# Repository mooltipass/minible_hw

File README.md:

# minible_hw
Repository for the Mini BLE Hardware

## Licenses

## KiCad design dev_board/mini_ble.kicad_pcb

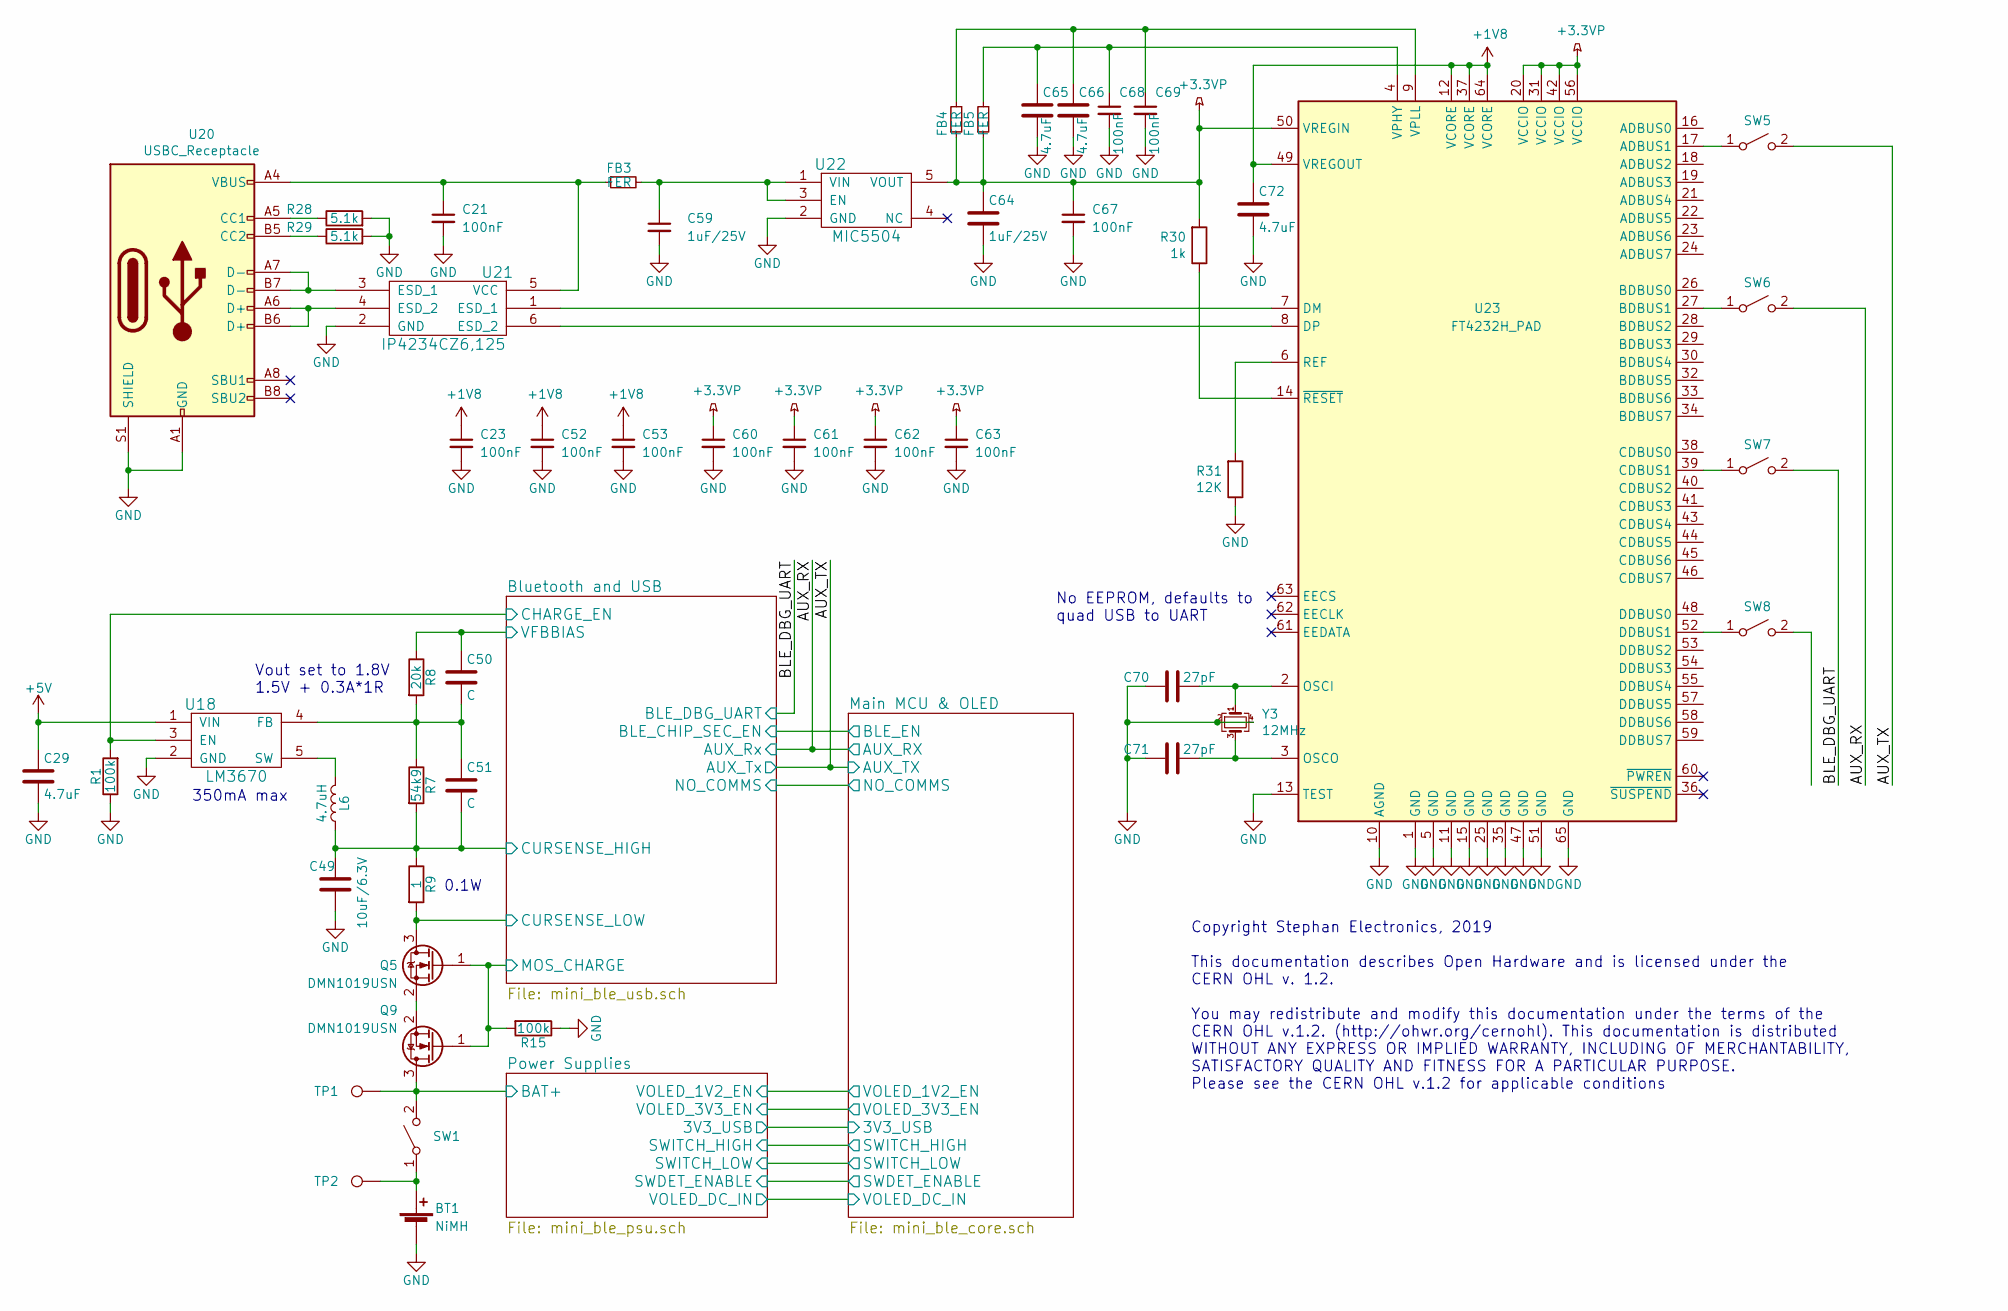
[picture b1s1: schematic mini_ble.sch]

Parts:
BT1: NiMH; BAT_TWOTHIRD_AAA
C21, C23, C52, C53, C60, C61, C62, C63, C67, C68, C69: 100nF; C_0603_1608Metric
C29, C65, C66, C72: 4.7uF; C_0603_1608Metric
C49: 10uF/6.3V; C_0603_1608Metric
C50, C51: C; C_0402_1005Metric
C59, C64: 1uF/25V; C_0603_1608Metric
C70, C71: 27pF; C_0402_1005Metric
FB3, FB4, FB5: FER; R_0603_1608Metric
L6: 4.7uH; L_0805_2012Metric
Q5, Q9: DMN1019USN; SC-59
R1, R15: 100k; R_0402_1005Metric
R7: 54k9; R_0402_1005Metric
R8: 20k; R_0402_1005Metric
R9: 1; R_0603_1608Metric
R28, R29: 5.1k; R_0402_1005Metric
R30: 1k; R_0402_1005Metric
R31: 12K; R_0402_1005Metric
SW1, SW5, SW6, SW7, SW8: SW_SPST; DIP_1POS_KAE01LAGT
TP1, TP2: TestPoint; TP_KEYSTONE_500X
U18: LM3670; SOT-23-5
U20: USBC_Receptacle; USB_C_Receptacle_GT-USB-7010
U21: IP4234CZ6,125; TSOP-6_1.65x3.05mm_P0.95mm
U22: MIC5504; SOT-23-5
U23: FT4232H_PAD; QFN-64-1EP_9x9mm_P0.5mm_EP4.35x4.35mm
Y3: 12MHz; Crystal_SMD_2520-4Pin_2.5x2.0mm

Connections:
+1V5: Q9.3 (D), SW1.2 (B), TP1.1; also elsewhere on the board
+1V8: C23.1, C52.1, C53.1, C72.1, U23.12 (VCORE), U23.37 (VCORE), U23.49 (VREGOUT), U23.64 (VCORE)
+3.3VP: C60.1, C61.1, C62.1, C63.1, C64.1, C67.1, FB4.1, FB5.1, R30.2, U22.5 (VOUT), U23.20 (VCCIO), U23.31 (VCCIO), U23.42 (VCCIO), U23.50 (VREGIN), U23.56 (VCCIO)
+5V: C29.1, U18.1 (VIN); also elsewhere on the board
/AUX_RX: SW6.2 (B); also elsewhere on the board
/AUX_TX: SW5.2 (B); also elsewhere on the board
/BLE_DBG_UART: SW7.2 (B); also elsewhere on the board
/Bluetooth and USB/CHARGE_EN: R1.2, U18.3 (EN); also elsewhere on the board
/Bluetooth and USB/CURSENSE_HIGH: C49.1, C51.2, L6.1, R7.2, R9.1; also elsewhere on the board
/Bluetooth and USB/CURSENSE_LOW: Q5.3 (D), R9.2; also elsewhere on the board
/Bluetooth and USB/MOS_CHARGE: Q5.1 (G), Q9.1 (G), R15.2; also elsewhere on the board
/Bluetooth and USB/VFBBIAS: C50.1, R8.1; also elsewhere on the board
GND: BT1.2 (-), C21.2, C23.2, C29.2, C49.2, C52.2, C53.2, C59.2, C60.2, C61.2, C62.2, C63.2, C64.2, C65.2, C66.2, C67.2, C68.2, C69.2, C70.1, C71.1, C72.2, R1.1, R15.1, R28.2, R29.2, R31.1, U18.2 (GND), U20.A1 (GND), U20.A12 (GND), U20.B1 (GND), U20.B12 (GND), U20.S1 (SHIELD), U21.2 (GND), U22.2 (GND), U23.1 (GND), U23.5 (GND), U23.10 (AGND), U23.11 (GND), U23.13 (TEST), U23.15 (GND), U23.25 (GND), U23.35 (GND), U23.47 (GND), U23.51 (GND), U23.65 (GND), Y3.2, Y3.4; also elsewhere on the board
unnamed: BT1.1 (+), SW1.1 (A), TP2.1
unnamed: C21.1, FB3.1, U20.A4 (VBUS), U20.A9 (VBUS), U20.B4 (VBUS), U20.B9 (VBUS), U21.5 (VCC)
unnamed: C50.2, C51.1, R7.1, R8.2, U18.4 (FB)
unnamed: C59.1, FB3.2, U22.1 (VIN), U22.3 (EN)
unnamed: C65.1, C68.1, FB5.2, U23.4 (VPHY)
unnamed: C66.1, C69.1, FB4.2, U23.9 (VPLL)
unnamed: C70.2, U23.2 (OSCI), Y3.1
unnamed: C71.2, U23.3 (OSCO), Y3.3
unnamed: L6.2, U18.5 (SW)
unnamed: Q5.2 (S), Q9.2 (S)
unnamed: R28.1, U20.A5 (CC1)
unnamed: R29.1, U20.B5 (CC2)
unnamed: R30.1, U23.14 (~RESET)
unnamed: R31.2, U23.6 (REF)
unnamed: SW5.1 (A), U23.17 (ADBUS1)
unnamed: SW6.1 (A), U23.27 (BDBUS1)
unnamed: SW7.1 (A), U23.39 (CDBUS1)
unnamed: SW8.1 (A), U23.52 (DDBUS1)
unnamed: U20.A6 (D+), U20.B6 (D+), U21.4 (ESD_2)
unnamed: U20.A7 (D-), U20.B7 (D-), U21.3 (ESD_1)
unnamed: U21.1 (ESD_1), U23.7 (DM)
unnamed: U21.6 (ESD_2), U23.8 (DP)

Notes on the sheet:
Copyright Stephan Electronics, 2019 This documentation describes Open Hardware and is licensed under the CERN OHL v. 1.2. You may redistribute and modify this documentation under the terms of the CERN OHL v.1.2. (http://ohwr.org/cernohl). This documentation is distributed WITHOUT ANY EXPRESS OR IMP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
350mA max
Vout set to 1.8V 1.5V + 0.3A*1R
0.1W
No EEPROM, defaults to quad USB to UART

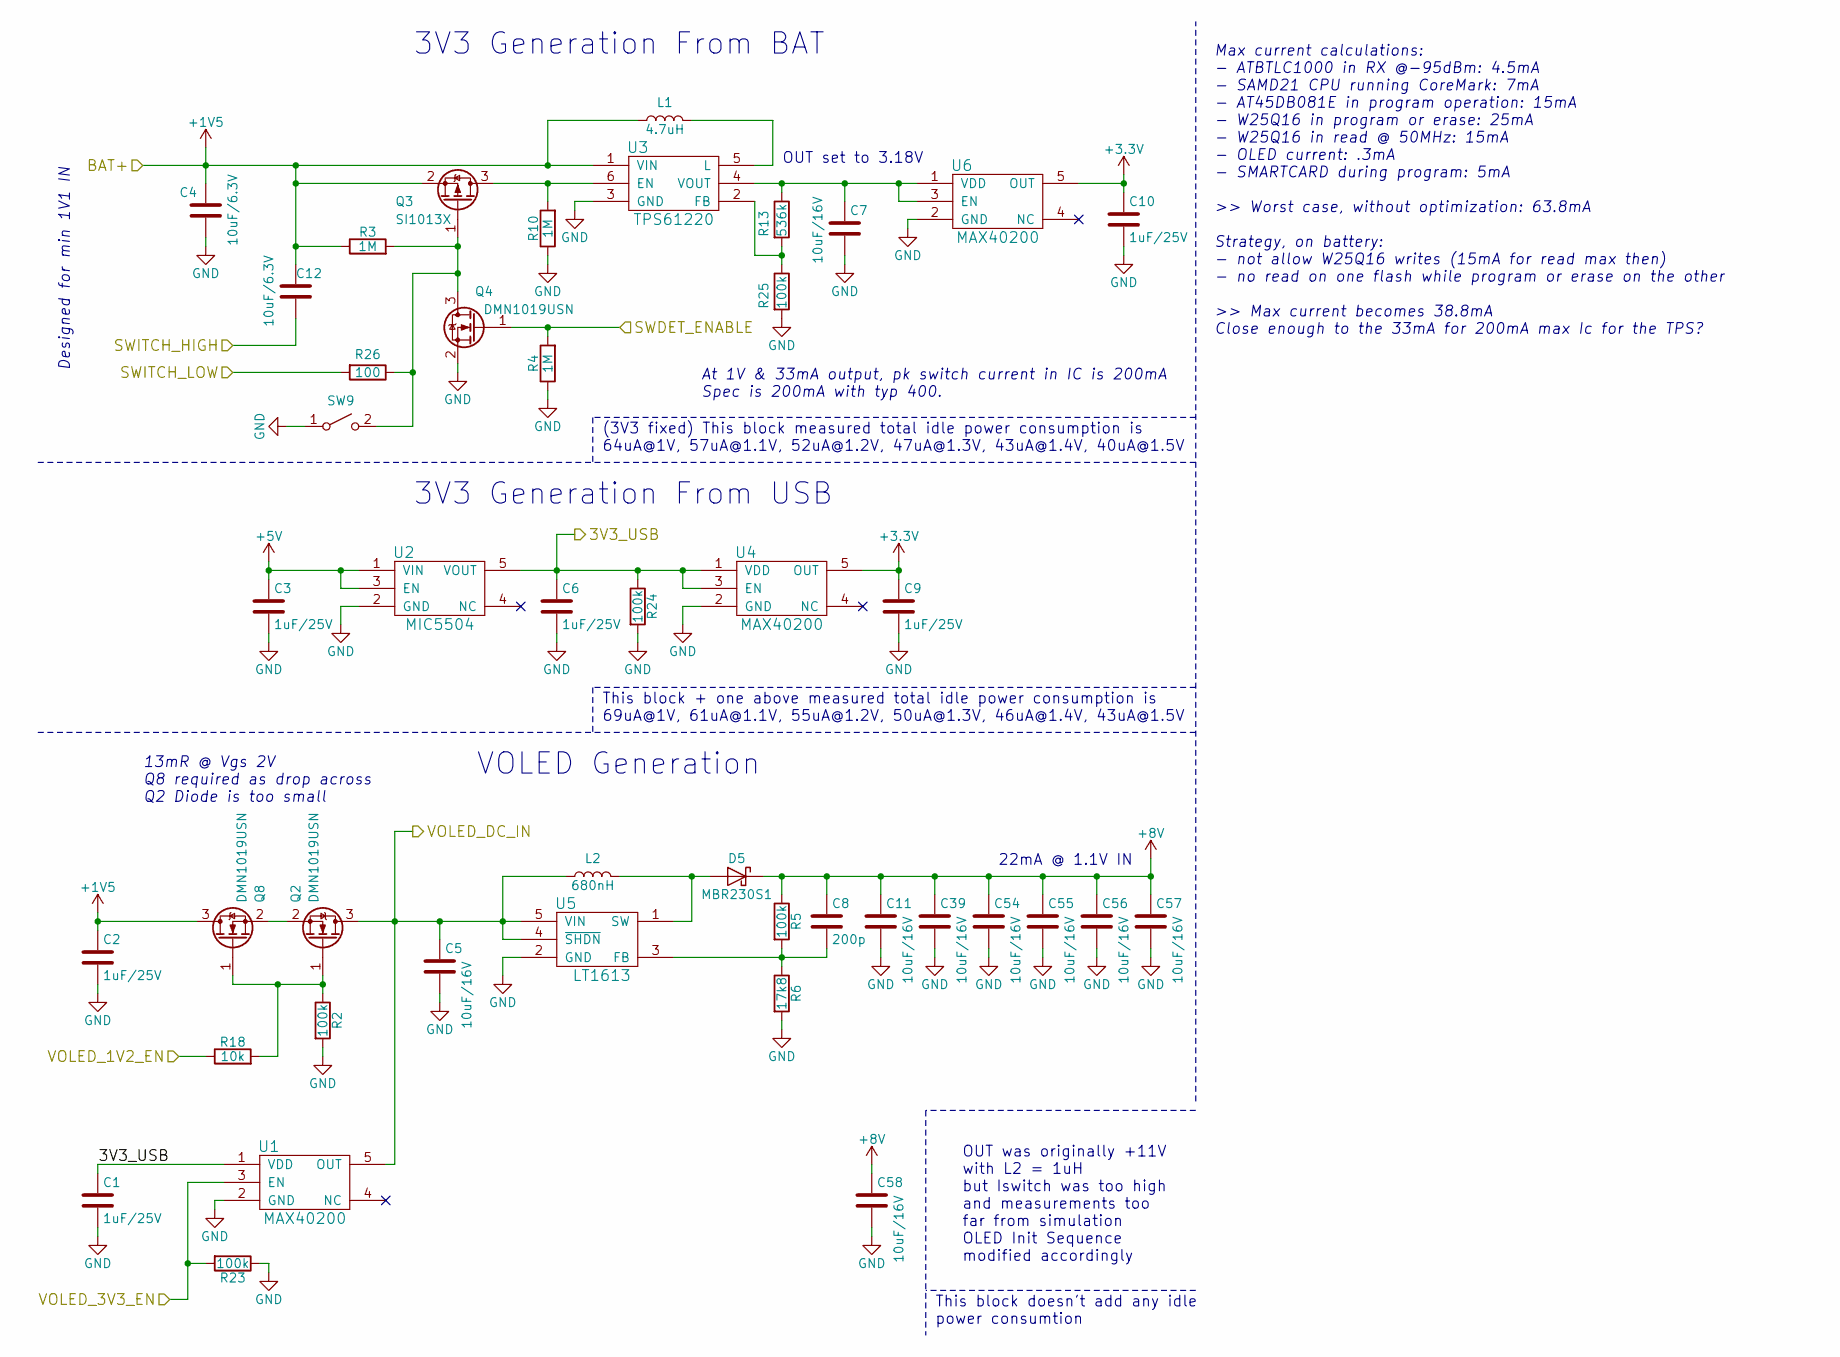
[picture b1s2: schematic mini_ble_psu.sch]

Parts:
C1, C2, C3, C6, C9, C10: 1uF/25V; C_0603_1608Metric
C4, C12: 10uF/6.3V; C_0603_1608Metric
C5, C7, C11, C39, C54, C55, C56, C57, C58: 10uF/16V; C_0805_2012Metric
C8: 200p; C_0402_1005Metric
D5: MBR230S1; D_SOD-123F
L1: 4.7uH; L_0805_2012Metric
L2: 680nH; L_0806
Q2, Q4, Q8: DMN1019USN; SC-59
Q3: SI1013X; SC89
R2, R5, R23, R24, R25: 100k; R_0402_1005Metric
R3, R4, R10: 1M; R_0402_1005Metric
R6: 17k8; R_0402_1005Metric
R13: 536k; R_0402_1005Metric
R18: 10k; R_0402_1005Metric
R26: 100; R_0402_1005Metric
SW9: SW_SPST; SWITCH_PUSH_6X3.5mm
U1, U4, U6: MAX40200; SOT-23-5
U2: MIC5504; SOT-23-5
U3: TPS61220; SOT-363_SC-70-6
U5: LT1613; TSOT-23-5

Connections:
+1V5: C2.1, C4.1, C12.1, L1.1, Q3.2 (S), Q8.3 (D), R3.1, U3.1 (VIN); also elsewhere on the board
+5V: C3.1, U2.1 (VIN), U2.3 (EN); also elsewhere on the board
+8V: C8.1, C11.1, C39.1, C54.1, C55.1, C56.1, C57.1, C58.1, D5.1 (K), R5.1; also elsewhere on the board
/Main MCU & OLED/3V3_USB: C1.1, C6.1, R24.1, U1.1 (VDD), U2.5 (VOUT), U4.1 (VDD), U4.3 (EN); also elsewhere on the board
/Main MCU & OLED/SWDET_ENABLE: Q4.1 (G), R4.2; also elsewhere on the board
/Main MCU & OLED/SWITCH_HIGH: C12.2; also elsewhere on the board
/Main MCU & OLED/SWITCH_LOW: R26.2; also elsewhere on the board
/Main MCU & OLED/VOLED_1V2_EN: R18.1; also elsewhere on the board
/Main MCU & OLED/VOLED_3V3_EN: R23.2, U1.3 (EN); also elsewhere on the board
/Main MCU & OLED/VOLED_DC_IN: C5.1, L2.1, Q2.3 (D), U1.5 (OUT), U5.4 (~SHDN), U5.5 (VIN); also elsewhere on the board
GND: C1.2, C2.2, C3.2, C4.2, C5.2, C6.2, C7.2, C9.2, C10.2, C11.2, C39.2, C54.2, C55.2, C56.2, C57.2, C58.2, Q4.2 (S), R2.2, R4.1, R6.2, R10.1, R23.1, R24.2, R25.2, SW9.1 (A), U1.2 (GND), U2.2 (GND), U3.3 (GND), U4.2 (GND), U5.2 (GND), U6.2 (GND); also elsewhere on the board
unnamed: C7.1, R13.1, U3.4 (VOUT), U6.1 (VDD), U6.3 (EN)
unnamed: C8.2, R5.2, R6.1, U5.3 (FB)
unnamed: D5.2 (A), L2.2, U5.1 (SW)
unnamed: L1.2, U3.5 (L)
unnamed: Q2.1 (G), Q8.1 (G), R2.1, R18.2
unnamed: Q2.2 (S), Q8.2 (S)
unnamed: Q3.1 (G), Q4.3 (D), R3.2, R26.1, SW9.2 (B)
unnamed: Q3.3 (D), R10.2, U3.6 (EN)
unnamed: R13.2, R25.1, U3.2 (FB)

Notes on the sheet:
3V3 Generation From USB
3V3 Generation From BAT
VOLED Generation
At 1V & 33mA output, pk switch current in IC is 200mA Spec is 200mA with typ 400.
Max current calculations: - ATBTLC1000 in RX @-95dBm: 4.5mA - SAMD21 CPU running CoreMark: 7mA - AT45DB081E in program operation: 15mA - W25Q16 in program or erase: 25mA - W25Q16 in read @ 50MHz: 15mA - OLED current: .3mA - SMARTCARD during program: 5mA >> Worst case, without optimization: 63.8mA S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
Designed for min 1V1 IN
13mR @ Vgs 2V Q8 required as drop across Q2 Diode is too small
(3V3 fixed) This block measured total idle power consumption is 64uA@1V, 57uA@1.1V, 52uA@1.2V, 47uA@1.3V, 43uA@1.4V, 40uA@1.5V
This block + one above measured total idle power consumption is 69uA@1V, 61uA@1.1V, 55uA@1.2V, 50uA@1.3V, 46uA@1.4V, 43uA@1.5V
This block doesn't add any idle power consumtion
22mA @ 1.1V IN
OUT was originally +11V with L2 = 1uH but Iswitch was too high and measurements too far from simulation OLED Init Sequence modified accordingly
OUT set to 3.18V

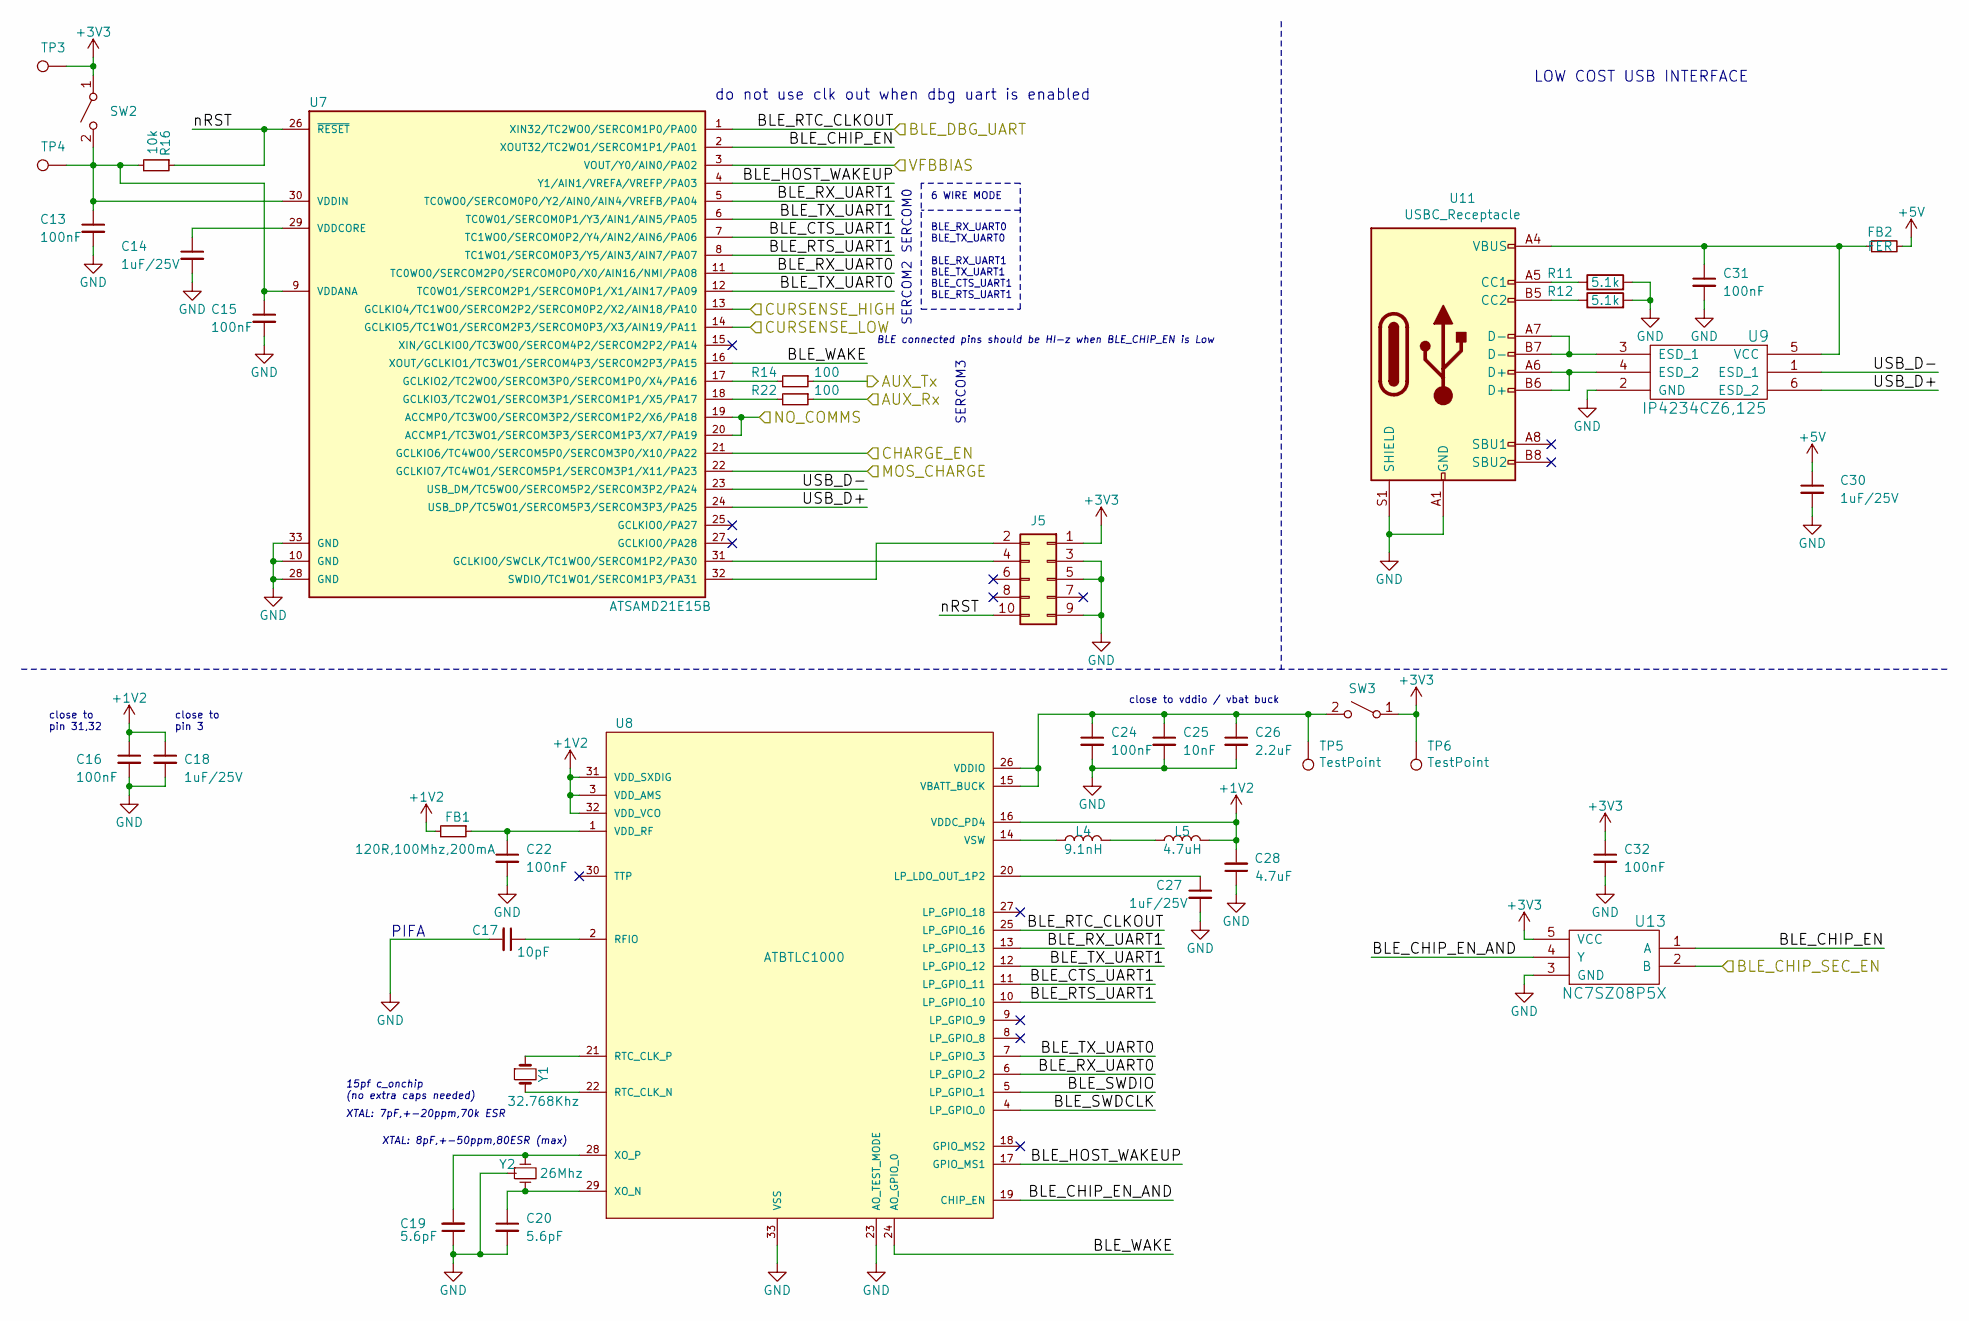
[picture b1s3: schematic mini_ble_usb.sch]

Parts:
C13, C15, C16, C22, C24, C31, C32: 100nF; C_0603_1608Metric
C14, C18, C27, C30: 1uF/25V; C_0603_1608Metric
C17: 10pF; C_0402_1005Metric
C19, C20: 5.6pF; C_0402_1005Metric
C25: 10nF; C_0603_1608Metric
C26: 2.2uF; C_0603_1608Metric
C28: 4.7uF; C_0603_1608Metric
FB1: 120R,100Mhz,200mA; R_0603_1608Metric
FB2: FER; R_0603_1608Metric
J5: Conn_02x05_Odd_Even; SHF-105-01-X-D-TH
L4: 9.1nH; L_0603_1608Metric
L5: 4.7uH; L_0805_2012Metric
R11, R12: 5.1k; R_0402_1005Metric
R14, R22: 100; R_0402_1005Metric
R16: 10k; R_0402_1005Metric
SW2, SW3: SW_SPST; DIP_1POS_KAE01LAGT
TP3, TP4, TP5, TP6: TestPoint; TP_KEYSTONE_500X
U7: ATSAMD21E15B; QFN-32-1EP_5x5mm_P0.5mm_EP3.7x3.7mm
U8: ATBTLC1000; QFN-32-1EP_4x4mm_Pitch0.4mm
U9: IP4234CZ6,125; TSOP-6_1.65x3.05mm_P0.95mm
U11: USBC_Receptacle; USB_C_Receptacle_GT-USB-7010
U13: NC7SZ08P5X; SOT-353_SC-70-5
Y1: 32.768Khz; Crystal_SMD_3215-2Pin_3.2x1.5mm
Y2: 26Mhz; Crystal_SMD_2016-4Pin_2.0x1.6mm

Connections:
+1V2: C16.1, C18.1, C28.2, FB1.2, L5.2, U8.3 (VDD_AMS), U8.16 (VDDC_PD4), U8.31 (VDD_SXDIG), U8.32 (VDD_VCO)
+5V: C30.1, FB2.2; also elsewhere on the board
/AUX_RX: R22.1; also elsewhere on the board
/AUX_TX: R14.1; also elsewhere on the board
/BLE_DBG_UART: U7.1 (XIN32/TC2WO0/SERCOM1P0/PA00), U8.25 (LP_GPIO_16); also elsewhere on the board
/Bluetooth and USB/BLE_CHIP_EN: U7.2 (XOUT32/TC2WO1/SERCOM1P1/PA01), U13.1 (A)
/Bluetooth and USB/BLE_CHIP_EN_AND: U8.19 (CHIP_EN), U13.4 (Y)
/Bluetooth and USB/BLE_CHIP_SEC_EN: U13.2 (B); also elsewhere on the board
/Bluetooth and USB/BLE_CTS_UART1: U7.7 (TC1WO0/SERCOM0P2/Y4/AIN2/AIN6/PA06), U8.11 (LP_GPIO_11)
/Bluetooth and USB/BLE_HOST_WAKEUP: U7.4 (Y1/AIN1/VREFA/VREFP/PA03), U8.17 (GPIO_MS1)
/Bluetooth and USB/BLE_RTS_UART1: U7.8 (TC1WO1/SERCOM0P3/Y5/AIN3/AIN7/PA07), U8.10 (LP_GPIO_10)
/Bluetooth and USB/BLE_RX_UART0: U7.11 (TC0WO0/SERCOM2P0/SERCOM0P0/X0/AIN16/NMI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), U8.6 (LP_GPIO_2)
/Bluetooth and USB/BLE_RX_UART1: U7.5 (TC0WO0/SERCOM0P0/Y2/AIN0/AIN4/VREFB/PA04), U8.13 (LP_GPIO_13)
/Bluetooth and USB/BLE_SWDCLK: U8.4 (LP_GPIO_0)
/Bluetooth and USB/BLE_SWDIO: U8.5 (LP_GPIO_1)
/Bluetooth and USB/BLE_TX_UART0: U7.12 (TC0WO1/SERCOM2P1/SERCOM0P1/X1/AIN17/PA09), U8.7 (LP_GPIO_3)
/Bluetooth and USB/BLE_TX_UART1: U7.6 (TC0W01/SERCOM0P1/Y3/AIN1/AIN5/PA05), U8.12 (LP_GPIO_12)
/Bluetooth and USB/BLE_WAKE: U7.16 (XOUT/GCLKIO1/TC3WO1/SERCOM4P3/SERCOM2P3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), U8.24 (AO_GPIO_0)
/Bluetooth and USB/CHARGE_EN: U7.21 (GCLKIO6/TC4WO0/SERCOM5P0/SERCOM3P0/X10/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); also elsewhere on the board
/Bluetooth and USB/CURSENSE_HIGH: U7.13 (GCLKIO4/TC1WO0/SERCOM2P2/SERCOM0P2/X2/A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); also elsewhere on the board
/Bluetooth and USB/CURSENSE_LOW: U7.14 (GCLKIO5/TC1WO1/SERCOM2P3/SERCOM0P3/X3/A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); also elsewhere on the board
/Bluetooth and USB/MOS_CHARGE: U7.22 (GCLKIO7/TC4WO1/SERCOM5P1/SERCOM3P1/X11/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); also elsewhere on the board
/Bluetooth and USB/NO_COMMS: U7.19 (ACCMP0/TC3WO0/SERCOM3P2/SERCOM1P2/X6/PA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), U7.20 (ACCMP1/TC3WO1/SERCOM3P3/SERCOM1P3/X7/PA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); also elsewhere on the board
/Bluetooth and USB/USB_D+: U7.24 (USB_DP/TC5WO1/SERCOM5P3/SERCOM3P3/PA25), U9.6 (ESD_2)
/Bluetooth and USB/USB_D-: U7.23 (USB_DM/TC5WO0/SERCOM5P2/SERCOM3P2/PA24), U9.1 (ESD_1)
/Bluetooth and USB/VFBBIAS: U7.3 (VOUT/Y0/AIN0/PA02); also elsewhere on the board
/Bluetooth and USB/nRST: J5.10, R16.1, U7.26 (~RESET~)
GND: C13.2, C14.2, C15.2, C16.2, C17.2, C18.2, C19.1, C20.2, C22.2, C24.2, C25.2, C26.2, C27.2, C28.1, C30.2, C31.2, C32.2, J5.3, J5.5, J5.9, R11.2, R12.2, U7.10 (GND), U7.28 (GND), U7.33 (GND), U8.23 (AO_TEST_MODE), U8.33 (VSS), U9.2 (GND), U11.A1 (GND), U11.A12 (GND), U11.B1 (GND), U11.B12 (GND), U11.S1 (SHIELD), U13.3 (GND), Y2.2, Y2.4; also elsewhere on the board
unnamed: C13.1, C15.1, R16.2, SW2.2 (B), TP4.1, U7.9 (VDDANA), U7.30 (VDDIN)
unnamed: C14.1, U7.29 (VDDCORE)
unnamed: C17.1, U8.2 (RFIO)
unnamed: C19.2, U8.28 (XO_P), Y2.1
unnamed: C20.1, U8.29 (XO_N), Y2.3
unnamed: C22.1, FB1.1, U8.1 (VDD_RF)
unnamed: C24.1, C25.1, C26.1, SW3.2 (B), TP5.1, U8.15 (VBATT_BUCK), U8.26 (VDDIO)
unnamed: C27.1, U8.20 (LP_LDO_OUT_1P2)
unnamed: C31.1, FB2.1, U9.5 (VCC), U11.A4 (VBUS), U11.A9 (VBUS), U11.B4 (VBUS), U11.B9 (VBUS)
unnamed: J5.2, U7.32 (SWDIO/TC1WO1/SERCOM1P3/PA31)
unnamed: J5.4, U7.31 (GCLKIO0/SWCLK/TC1WO0/SERCOM1P2/PA30)
unnamed: L4.1, U8.14 (VSW)
unnamed: L4.2, L5.1
unnamed: R11.1, U11.A5 (CC1)
unnamed: R12.1, U11.B5 (CC2)
unnamed: R14.2, U7.17 (GCLKIO2/TC2WO0/SERCOM3P0/SERCOM1P0/X4/P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)
unnamed: R22.2, U7.18 (GCLKIO3/TC2WO1/SERCOM3P1/SERCOM1P1/X5/P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)
unnamed: U8.21 (RTC_CLK_P), Y1.1
unnamed: U8.22 (RTC_CLK_N), Y1.2
unnamed: U9.4 (ESD_2), U11.A6 (D+), U11.B6 (D+)
unnamed: U9.3 (ESD_1), U11.A7 (D-), U11.B7 (D-)

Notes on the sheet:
XTAL: 8pF,+-50ppm,80ESR (max)
XTAL: 7pF,+-20ppm,70k ESR
15pf c_onchip (no extra caps needed)
BLE connected pins should be HI-z when BLE_CHIP_EN is Low
close to vddio / vbat buck
LOW COST USB INTERFACE
close to pin 3
close to pin 31,32
SERCOM3
SERCOM2
SERCOM0
6 WIRE MODE
BLE_RX_UART0 BLE_TX_UART0 BLE_RX_UART1 BLE_TX_UART1 BLE_CTS_UART1 BLE_RTS_UART1
PIFA
do not use clk out when dbg uart is enabled

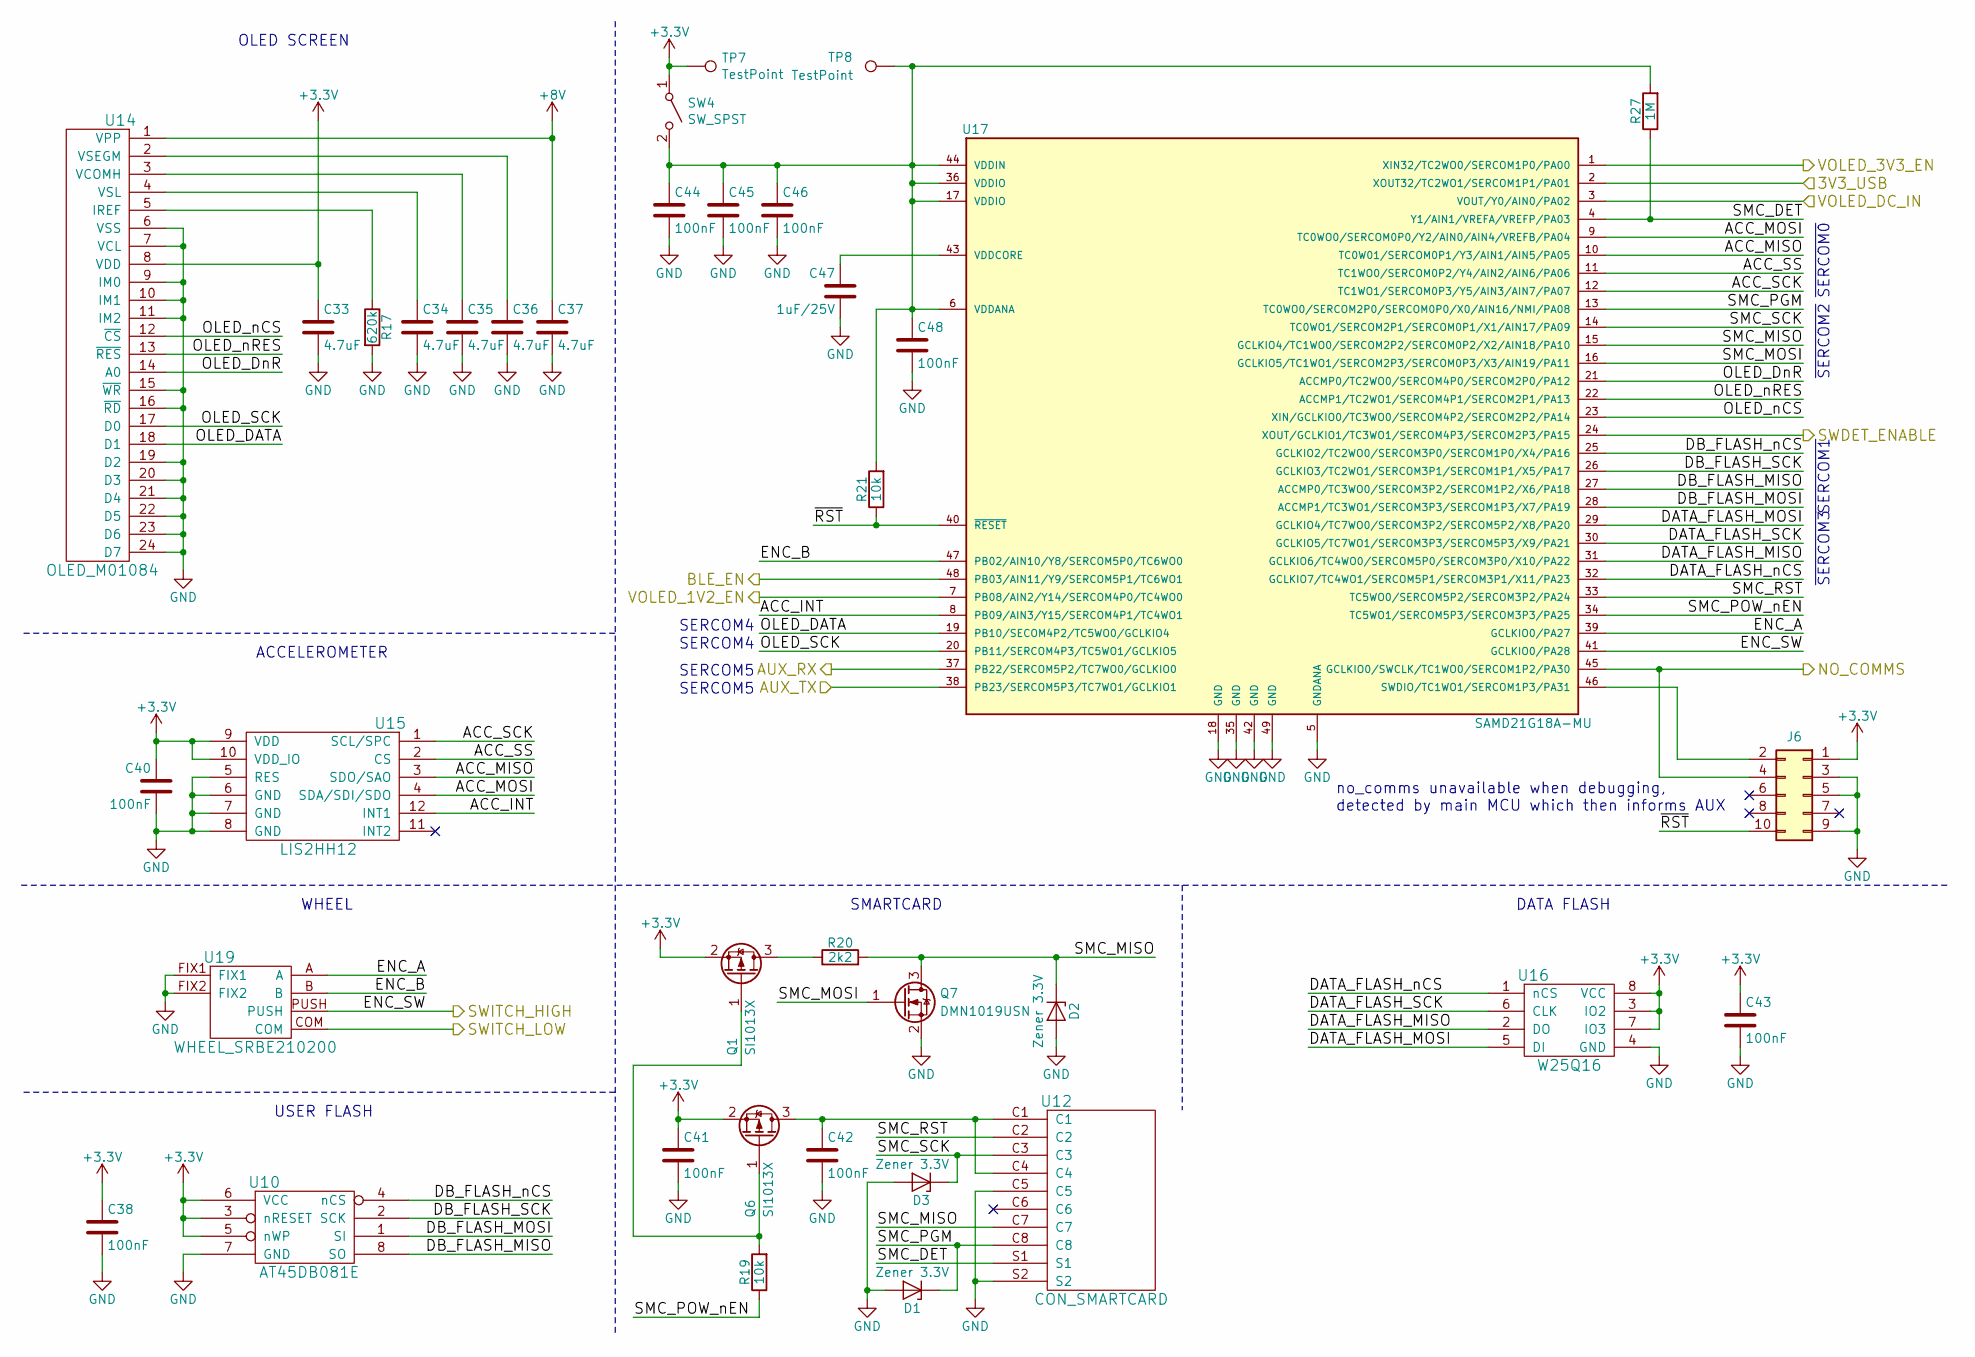
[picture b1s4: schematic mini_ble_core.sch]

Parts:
C33, C34, C35, C36, C37: 4.7uF; C_0603_1608Metric
C38, C40, C41, C42, C43, C44, C45, C46, C48: 100nF; C_0603_1608Metric
C47: 1uF/25V; C_0603_1608Metric
D1, D2, D3: Zener 3.3V; D_SOD-523
J6: Conn_02x05_Odd_Even; SHF-105-01-X-D-TH
Q1, Q6: SI1013X; SC89
Q7: DMN1019USN; SC-59
R17: 620k; R_0603_1608Metric
R19, R21: 10k; R_0402_1005Metric
R20: 2k2; R_0603_1608Metric
R27: 1M; R_0402_1005Metric
SW4: SW_SPST; DIP_1POS_KAE01LAGT
TP7, TP8: TestPoint; TP_KEYSTONE_500X
U10: AT45DB081E; SOIC-8_3.9x4.9mm_P1.27mm
U12: CON_SMARTCARD; CON_SMARTCARD_CLONE_91-90473-003A
U14: OLED_M01084; SCREEN_M01084
U15: LIS2HH12; LGA-12
U16: W25Q16; SOIC-8_3.9x4.9mm_P1.27mm
U17: SAMD21G18A-MU; QFN-48-1EP_7x7mm_P0.5mm_EP5.3x5.3mm
U19: WHEEL_SRBE210200; SRBE210200

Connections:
+8V: C37.1, U14.1 (VPP); also elsewhere on the board
/AUX_RX: U17.37 (PB22/SERCOM5P2/TC7WO0/GCLKIO0); also elsewhere on the board
/AUX_TX: U17.38 (PB23/SERCOM5P3/TC7WO1/GCLKIO1); also elsewhere on the board
/Bluetooth and USB/BLE_CHIP_SEC_EN: U17.48 (PB03/AIN11/Y9/SERCOM5P1/TC6WO1); also elsewhere on the board
/Bluetooth and USB/NO_COMMS: J6.4, U17.45 (GCLKIO0/SWCLK/TC1WO0/SERCOM1P2/PA30); also elsewhere on the board
/Main MCU & OLED/3V3_USB: U17.2 (XOUT32/TC2WO1/SERCOM1P1/PA01); also elsewhere on the board
/Main MCU & OLED/ACC_INT: U15.12 (INT1), U17.8 (PB09/AIN3/Y15/SERCOM4P1/TC4WO1)
/Main MCU & OLED/ACC_MISO: U15.3 (SDO/SAO), U17.10 (TC0W01/SERCOM0P1/Y3/AIN1/AIN5/PA05)
/Main MCU & OLED/ACC_MOSI: U15.4 (SDA/SDI/SDO), U17.9 (TC0WO0/SERCOM0P0/Y2/AIN0/AIN4/VREFB/PA04)
/Main MCU & OLED/ACC_SCK: U15.1 (SCL/SPC), U17.12 (TC1WO1/SERCOM0P3/Y5/AIN3/AIN7/PA07)
/Main MCU & OLED/ACC_SS: U15.2 (CS), U17.11 (TC1WO0/SERCOM0P2/Y4/AIN2/AIN6/PA06)
/Main MCU & OLED/DATA_FLASH_MISO: U16.2 (DO), U17.31 (GCLKIO6/TC4WO0/SERCOM5P0/SERCOM3P0/X10/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)
/Main MCU & OLED/DATA_FLASH_MOSI: U16.5 (DI), U17.29 (GCLKIO4/TC7WO0/SERCOM3P2/SERCOM5P2/X8/P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)
/Main MCU & OLED/DATA_FLASH_SCK: U16.6 (CLK), U17.30 (GCLKIO5/TC7WO1/SERCOM3P3/SERCOM5P3/X9/P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)
/Main MCU & OLED/DATA_FLASH_nCS: U16.1 (nCS), U17.32 (GCLKIO7/TC4WO1/SERCOM5P1/SERCOM3P1/X11/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)
/Main MCU & OLED/DB_FLASH_MISO: U10.8 (SO), U17.27 (ACCMP0/TC3WO0/SERCOM3P2/SERCOM1P2/X6/PA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)
/Main MCU & OLED/DB_FLASH_MOSI: U10.1 (SI), U17.28 (ACCMP1/TC3WO1/SERCOM3P3/SERCOM1P3/X7/PA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)
/Main MCU & OLED/DB_FLASH_SCK: U10.2 (SCK), U17.26 (GCLKIO3/TC2WO1/SERCOM3P1/SERCOM1P1/X5/P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)
/Main MCU & OLED/DB_FLASH_nCS: U10.4 (nCS), U17.25 (GCLKIO2/TC2WO0/SERCOM3P0/SERCOM1P0/X4/P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)
/Main MCU & OLED/ENC_A: U17.39 (GCLKIO0/PA27), U19.A
/Main MCU & OLED/ENC_B: U17.47 (PB02/AIN10/Y8/SERCOM5P0/TC6WO0), U19.B
/Main MCU & OLED/OLED_DATA: U14.18 (D1), U17.19 (PB10/SECOM4P2/TC5WO0/GCLKIO4)
/Main MCU & OLED/OLED_DnR: U14.14 (A0), U17.21 (ACCMP0/TC2WO0/SERCOM4P0/SERCOM2P0/PA12)
/Main MCU & OLED/OLED_SCK: U14.17 (D0), U17.20 (PB11/SERCOM4P3/TC5WO1/GCLKIO5)
/Main MCU & OLED/OLED_nCS: U14.12 (~CS), U17.23 (XIN/GCLKIO0/TC3WO0/SERCOM4P2/SERCOM2P2/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)
/Main MCU & OLED/OLED_nRES: U14.13 (~RES), U17.22 (ACCMP1/TC2WO1/SERCOM4P1/SERCOM2P1/PA13)
/Main MCU & OLED/SMC_DET: R27.1, U12.S1, U17.4 (Y1/AIN1/VREFA/VREFP/PA03)
/Main MCU & OLED/SMC_MISO: D2.1 (K), Q7.3 (D), R20.2, U12.C7, U17.15 (GCLKIO4/TC1WO0/SERCOM2P2/SERCOM0P2/X2/A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)
/Main MCU & OLED/SMC_MOSI: Q7.1 (G), U17.16 (GCLKIO5/TC1WO1/SERCOM2P3/SERCOM0P3/X3/A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)
/Main MCU & OLED/SMC_PGM: D1.1 (K), U12.C8, U17.13 (TC0WO0/SERCOM2P0/SERCOM0P0/X0/AIN16/NMI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)
/Main MCU & OLED/SMC_POW_nEN: R19.1, U17.34 (TC5WO1/SERCOM5P3/SERCOM3P3/PA25)
/Main MCU & OLED/SMC_RST: U12.C2, U17.33 (TC5WO0/SERCOM5P2/SERCOM3P2/PA24)
/Main MCU & OLED/SMC_SCK: D3.1 (K), U12.C3, U17.14 (TC0WO1/SERCOM2P1/SERCOM0P1/X1/AIN17/PA09)
/Main MCU & OLED/SWDET_ENABLE: U17.24 (XOUT/GCLKIO1/TC3WO1/SERCOM4P3/SERCOM2P3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); also elsewhere on the board
/Main MCU & OLED/SWITCH_HIGH: U17.41 (GCLKIO0/PA28), U19.PUSH; also elsewhere on the board
/Main MCU & OLED/SWITCH_LOW: U19.COM; also elsewhere on the board
/Main MCU & OLED/VOLED_1V2_EN: U17.7 (PB08/AIN2/Y14/SERCOM4P0/TC4WO0); also elsewhere on the board
/Main MCU & OLED/VOLED_3V3_EN: U17.1 (XIN32/TC2WO0/SERCOM1P0/PA00); also elsewhere on the board
/Main MCU & OLED/VOLED_DC_IN: U17.3 (VOUT/Y0/AIN0/PA02); also elsewhere on the board
/Main MCU & OLED/~RST: J6.10, R21.1, U17.40 (~RESET~)
GND: C33.2, C34.2, C35.2, C36.2, C37.2, C38.2, C40.2, C41.2, C42.2, C43.2, C44.2, C45.2, C46.2, C47.2, C48.2, D1.2 (A), D2.2 (A), D3.2 (A), J6.3, J6.5, J6.9, Q7.2 (S), R17.2, U10.7 (GND), U12.C5, U12.S2, U14.6 (VSS), U14.7 (VCL), U14.9 (IM0), U14.10 (IM1), U14.11 (IM2), U14.15 (~WR), U14.16 (~RD), U14.19 (D2), U14.20 (D3), U14.21 (D4), U14.22 (D5), U14.23 (D6), U14.24 (D7), U15.5 (RES), U15.6 (GND), U15.7 (GND), U15.8 (GND), U16.4 (GND), U17.5 (GNDANA), U17.18 (GND), U17.35 (GND), U17.42 (GND), U17.49 (GND), U19.FIX1, U19.FIX2; also elsewhere on the board
unnamed: C34.1, U14.4 (VSL)
unnamed: C35.1, U14.3 (VCOMH)
unnamed: C36.1, U14.2 (VSEGM)
unnamed: C42.1, Q6.3 (D), U12.C1, U12.C4
unnamed: C44.1, C45.1, C46.1, C48.1, R21.2, R27.2, SW4.2 (B), TP8.1, U17.6 (VDDANA), U17.17 (VDDIO), U17.36 (VDDIO), U17.44 (VDDIN)
unnamed: C47.1, U17.43 (VDDCORE)
unnamed: J6.2, U17.46 (SWDIO/TC1WO1/SERCOM1P3/PA31)
unnamed: Q1.1 (G), Q6.1 (G), R19.2
unnamed: Q1.3 (D), R20.1
unnamed: R17.1, U14.5 (IREF)

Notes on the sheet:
OLED SCREEN
ACCELEROMETER
WHEEL
USER FLASH
SMARTCARD
DATA FLASH
SERCOM5
~SERCOM1
SERCOM4
~SERCOM3
~SERCOM0
~SERCOM2
no_comms unavailable when debugging, detected by main MCU which then informs AUX

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

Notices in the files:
dev_board/mini_ble.kicad_pcb:
CERN OHL / Stephan Electronics
